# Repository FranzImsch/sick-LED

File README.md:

# Sick LED Driver

## [Schematic](https://franz.science/sick-LED/Schematic.pdf)
## [iBOM](https://franz.science/sick-LED/Hardware/KiCad-Files/bom/index.html)
  
**\*Work in progress\***

Six channel LED driver board that is built around the [LZ7-04-M2PD](https://www.osram.com/ecat/LED%20ENGIN%20LuxiGen%20LZ7-04M2PD/com/en/class_pim_web_catalog_103489/prd_pim_device_13582430/) on MCPCB from LED Engin.

 It's a 60W LED with six colours, which can be used to do some adjustable white experiments due to the relatively full spectrum of the LED (at least compared to a normal RGB-LED): 

The project's objective is not to build an LED that is as bright as possible but to create a dev board that makes it easy to study RGBALC LEDs. Thus, the board is powered via USB-PD and programmed with Arduino.

## Hardware
The PCB is mounted on a heatsink (100x100x40mm black anodised aluminium) using four M3 screws. Two 40mm fans could be attached to the heatsink and powered using the provided 2.54mm headers (the thermal characteristics of the whole design have not been tested yet).  

### Known (Hardware) Bugs
* Each PWM Channel had to be pulled down with a 4.7kΩ resistor.
* FAN1 pin (PB5, TIM3_CH2) cannot be used as PWM output when Hardware-I2C is initialised (Ch. 2.8.7 [ST Errata Sheet](https://www.st.com/resource/en/errata_sheet/es093-stm32f100x4-stm32f100x6-stm32f100x8-and-stm32f100xb-low-and-mediumdensity-value-line-device-limitations-stmicroelectronics.pdf)).

### Fusion360 online viewer
https://a360.co/2VWAmD9

#### LED Driver (BP1808)
\*Docu\*

#### MCU
\*Docu\*

#### USB-C PD Chip
\*Docu\*

#### Buck Converter
\*Docu\*

#### RS-485 Transceiver
\*Docu\*

#### Microphone Amplifier
\*Docu\*

#### Light Sensor
\*Docu\*

## Software
To this point, the software is very basic. It allows the individual channels to be controlled from a computer (Linux or macOS) with [QLC+](https://www.qlcplus.org). It therefore pretends to be a nanoDMX device (No nanoDMX implementation in QLC+ on Windows, apparently).  
The buttons, microphone, light sensor and DMX interface are not yet implemented.  
The software should be rewritten using STM32Cube framework (in progress™).

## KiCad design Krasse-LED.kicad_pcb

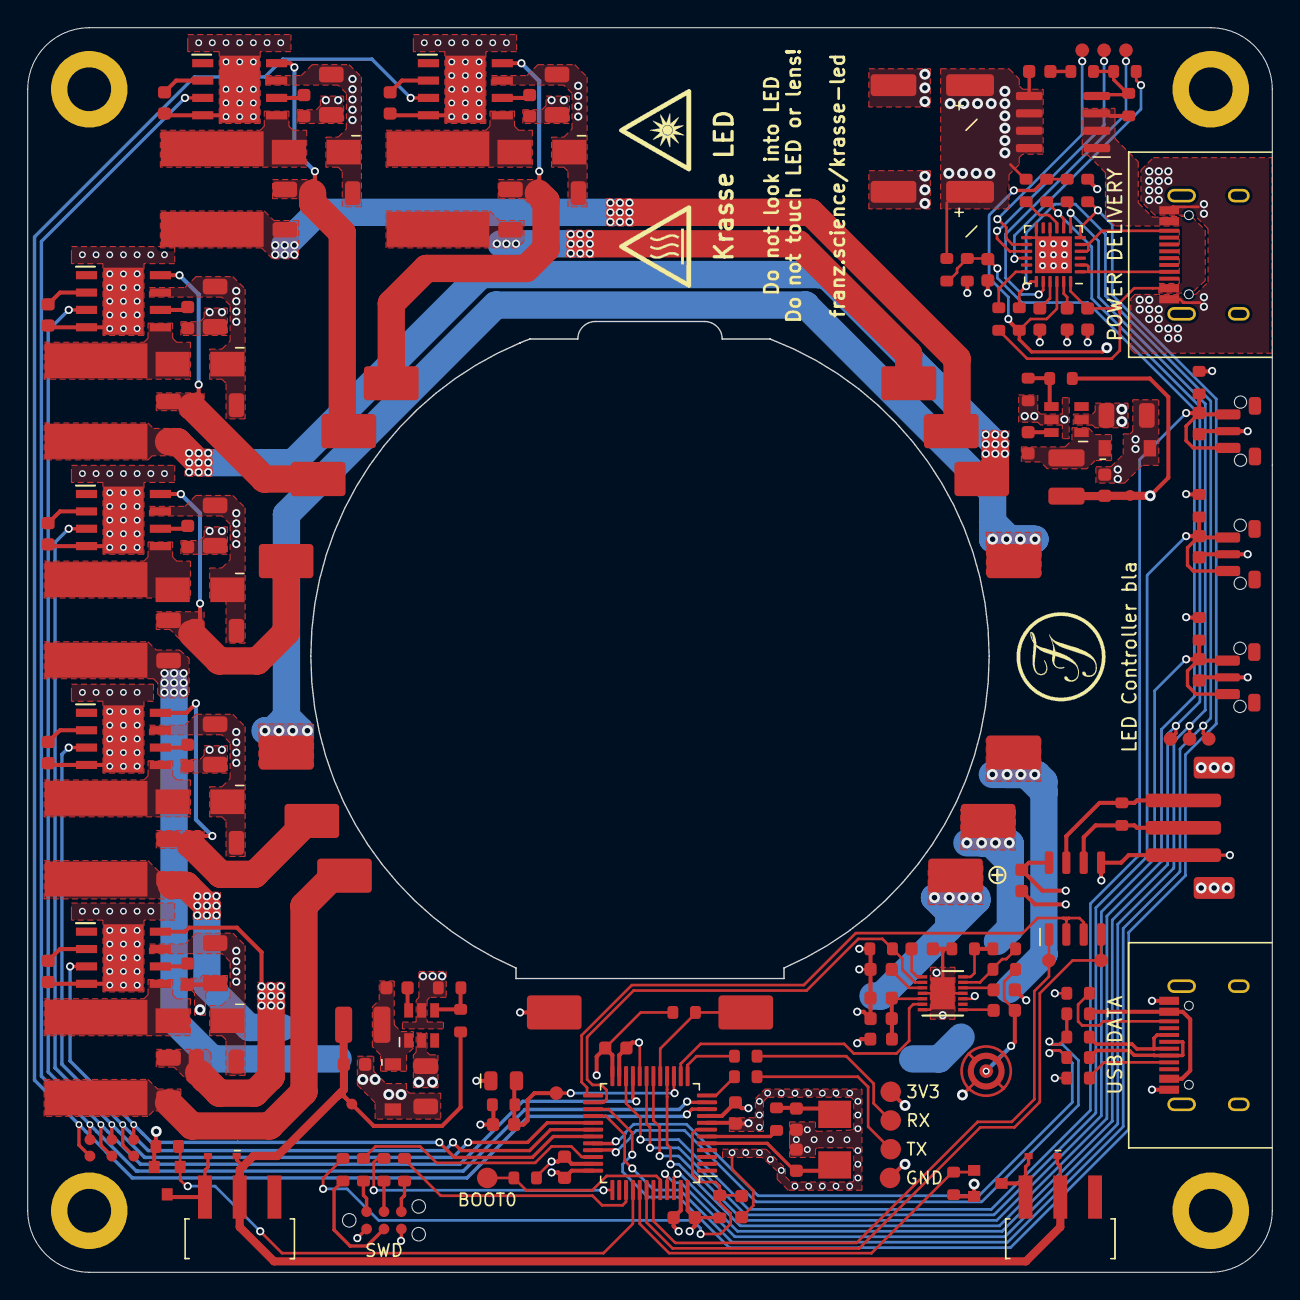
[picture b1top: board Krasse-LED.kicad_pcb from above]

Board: 4 copper layers, 91.0 x 91.0 mm, 175 parts (0 on the bottom side), 112 nets.

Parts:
C1, C2, C46, C54: 22nF; C_0603_1608Metric
C3, C4, C5: 100nF (Y5V); C_0603_1608Metric
C6, C8, C10, C12, C16, C17, C18, C19, C52: 100nF; C_0603_1608Metric
C7: 0.47µF; C_0603_1608Metric
C9: 2.2µF; C_0603_1608Metric
C11, C21, C28, C29, C30, C31, C32, C44, C45: 1µF; C_0603_1608Metric
C13, C38, C39, C40, C41, C42: 2.2µF; C_1206_3216Metric
C14, C15: 30pF; C_0603_1608Metric
C20, C23, C24, C25, C26, C27: 4.7nF; C_0603_1608Metric
C22, C33, C34, C35, C36, C37, C47, C50: 10µF; C_1206_3216Metric
C43: 47nF; C_0603_1608Metric
C48, C53: 15µF; C_Elec_6.3x5.5_WE
C49, C51, C55: 4.7µF; C_0603_1608Metric
D1, D3, D4, D5, D6, D7: SS34; D_SMA
D2: LZ7-04M2PD-PCB
D8, D9: DSS34; D_SOD-123
D11, D12: 1N4148WS; D_SOD-323
FB1: 120Ω; L_0603_1608Metric
H1, H2, H3, H4: M3; MountingHole_3.2mm_M3_DIN965_Pad
J2: TC2030; Tag-Connect_TC2030-IDC-NL_2x03_P1.27mm_Vertical
J3: DMX; JST_PH_B3B-PH-SM4-TB_1x03-1MP_P2.00mm_Vertical
J4, J6: USB_C_Receptacle_USB2.0; USB_C_Receptacle_HRO_TYPE-C-31-M-12
J7: FAN 1; PinHeader_1x03_P2.54mm_Horizontal_SMD_Pin1Left
J8: FAN 2; PinHeader_1x03_P2.54mm_Horizontal_SMD_Pin1Left
L1, L2, L3, L4, L5, L6: 10µH; L_Chilisin_8040
L7, L8: 4.7µH; L_1210_3225Metric
MK1: Microphone_Condenser; B4013AM423-093
Q1: Senba SMD0805-20; LED_0805_2012Metric
Q2: AO4407A; SOIC-8_3.9x4.9mm_P1.27mm
Q3, Q4: AO3400A; SOT-23
R1, R8, R38: 100kΩ; R_0603_1608Metric
R2: 18kΩ; R_0603_1608Metric
R3, R4, R5, R12: 10k; R_0603_1608Metric
R6: ca. 10k; R_0603_1608Metric
R7: 6.2kΩ; R_0603_1608Metric
R9: 150kΩ; R_0603_1608Metric
R10: 2.21kΩ; R_0603_1608Metric
R11: 120Ω; R_0603_1608Metric
R13, R19, R20, R21, R22: 0.2Ω; R_1206_3216Metric
R14, R17: 5.1kΩ; R_0603_1608Metric
R15, R16: 20Ω; R_0603_1608Metric
R18, R31, R32, R45: 4.7kΩ; R_0603_1608Metric
R23: 0.21Ω; R_1206_3216Metric
R24, R25, R26, R27, R33, R34: 22Ω; R_0603_1608Metric
R28, R29, R36, R41, R44: 10kΩ; R_0603_1608Metric
R30: 0Ω; R_0603_1608Metric
R35, R37: 1kΩ; R_0603_1608Metric
R39: 22kΩ; R_0603_1608Metric
R40: 100Ω; R_0603_1608Metric
R42, R46: 50kΩ; R_0603_1608Metric
R43: 16.265kΩ; R_0603_1608Metric
R47: 3.62kΩ; R_0603_1608Metric
SW1, SW2, SW3: SW_Push; SW_Push_1P1T-MP_NO_Horizontal_Alps_SKRTLAE010
TP1: RX1; TestPoint_Pad_D1.0mm
TP2: TX1; TestPoint_Pad_D1.0mm
TP3: SDA; TestPoint_Pad_D1.0mm
TP4: SCL; TestPoint_Pad_D1.0mm
TP6: Light Sensor; TestPoint_Pad_D1.0mm
TP7: BOOT 0; TestPoint_Pad_D1.5mm
TP8: R; TestPoint_Pad_D0.8mm
TP9: B; TestPoint_Pad_D0.8mm
TP10: G; TestPoint_Pad_D0.8mm
TP11: L; TestPoint_Pad_D0.8mm
TP12: A; TestPoint_Pad_D0.8mm
TP13: C; TestPoint_Pad_D0.8mm
TP14: ALERT; TestPoint_Pad_D1.0mm
TP15: PWROK2; TestPoint_Pad_D1.0mm
TP16: PWROK3; TestPoint_Pad_D1.0mm
TP17: GPIO; TestPoint_Pad_D1.0mm
TP18: 3.3V; TestPoint_Pad_D0.8mm
TP19: 12V; TestPoint_Pad_D0.8mm
TP20: 3.3V; TestPoint_Pad_D1.5mm
TP21: TX; TestPoint_Pad_D1.5mm
TP22: RX; TestPoint_Pad_D1.5mm
TP23: GND; TestPoint_Pad_D1.5mm
U1: STM32F103C8Tx; LQFP-48_7x7mm_P0.5mm
U2: MAX9814; DFN-14-1EP_3x3mm_P0.4mm_EP1.78x2.35mm
U3: MAX3485; SOP-8_3.9x4.9mm_P1.27mm
U4, U5, U6, U7, U8, U9: BP1808; Texas_HSOP-8-1EP_3.9x4.9mm_P1.27mm
U10, U12: ACT4088; SOT-23-6
U11: STUSB4500QTR; QFN-24-1EP_4x4mm_P0.5mm_EP2.7x2.7mm
Y1: 8MHz; Crystal_SMD_5032-2Pin_5.0x3.2mm

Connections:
+3V3: C10.1, C16.1, C17.1, C18.1, C19.1, C49.1, FB1.1, J2.1, L7.2, Q1.1, R3.2, R4.2, R5.2, R7.1, R29.2, R31.2, R32.1, R42.1, R45.2, TP18.1, TP20.1, U1.9, U1.24, U1.36, U1.48, U2.10, U3.8, U11.22
+12V: C55.1, D11.1, D12.1, J7.2, J8.2, L8.2, R46.1, TP19.1
/3V3-ANALOG: C11.1, C12.1, FB1.2, U2.5
/AGC-Th: R8.2, R9.1, U2.14
/AmpBias: C7.2, U2.12
/Boostrap-3V3: C46.1, U10.6
/Boostrap-12V: C54.1, U12.6
/CC1-DATA: J4.A5, R17.1
/CC1-PD: J6.A5, U11.1, U11.2
/CC2-DATA: J4.B5, R14.1
/CC2-PD: J6.B5, U11.4, U11.5
/COMP-A: C26.2, U8.2
/COMP-B: C23.2, U5.2
/COMP-C: C27.2, U9.2
/COMP-G: C24.2, U6.2
/COMP-L: C25.2, U7.2
/COMP-R: C20.2, U4.2
/D+: J4.A6, J4.B6, R16.2
/D-: J4.A7, J4.B7, R15.2
/DC-Offs-Adj: C9.1, U2.3
/DISCH: R37.2, U11.9
/DMX_N: J3.2, R11.1, U3.6
/DMX_P: J3.1, R11.2, U3.7
/J-CLK: J2.4, R26.2
/J-DIO: J2.2, R25.2
/J-RESET: J2.3, R24.1
/J-SWO: J2.6, R27.2
/LED-A-A: C41.1, D2.6, R22.1, U8.8
/LED-A-C: C41.2, D2.9, L5.2
/LED-B-A: C38.1, D2.2, R19.1, U5.8
/LED-B-C: C38.2, D2.13, L2.2
/LED-C-A: C42.1, D2.8, R23.1, U9.8
/LED-C-C: C42.2, D2.7, L6.2
/LED-G-A: C39.1, D2.3, R20.1, U6.8
/LED-G-C: C39.2, D2.12, L3.2
/LED-L-A: C40.1, D2.4, R21.1, U7.8
/LED-L-C: C40.2, D2.10, L4.2
/LED-R-A: C13.1, D2.1, R13.1, U4.8
/LED-R-C: C13.2, D2.14, L1.2
/LIME-SERIES: D2.5, D2.11
/MIC+: C6.2, MK1.+, R10.2
/MICBIAS: R9.2, R10.1, U2.13
/MICIN: C6.1, U2.8
/PD-GPIO: TP17.1, U11.15
/PWROK2: TP15.1, U11.20
/PWROK3: TP16.1, U11.14
/RX-IN: R34.2, TP22.1
/SW-3V3: C46.2, D8.1, L7.1, U10.1
/SW-12V: C54.2, D9.1, L8.1, U12.1
/SW-A: D6.2, L5.1, U8.5
/SW-B: D3.2, L2.1, U5.5
/SW-C: D7.2, L6.1, U9.5
/SW-G: D4.2, L3.1, U6.5
/SW-L: D5.2, L4.1, U7.5
/SW-R: D1.2, L1.1, U4.5
/TX-IN: R33.2, TP21.1
/TimingCap: C8.1, U2.1
/VBUS-Disch: R35.1, U11.18
/VBUS-PD: C51.1, J6.A4, J6.A9, J6.B4, J6.B9, Q2.1, Q2.2, Q2.3, R35.2, R38.2, U11.24
/VDD-A: C31.2, U8.6
/VDD-B: C28.2, U5.6
/VDD-C: C32.2, U9.6
/VDD-G: C29.2, U6.6
/VDD-L: C30.2, U7.6
/VDD-R: C21.2, U4.6
BOOT0: R28.1, TP7.1, U1.44
BTN_1: C3.2, R3.1, SW1.1, U1.18
BTN_2: C4.2, R4.1, SW2.1, U1.19
BTN_3: C5.2, R5.1, SW3.1, U1.22
DIM_AMBER: TP12.1, U1.30, U8.3
DIM_BLUE: TP9.1, U1.11, U5.3
DIM_CYAN: TP13.1, U1.31, U9.3
DIM_GREEN: TP10.1, U1.21, U6.3
DIM_LIME: TP11.1, U1.29, U7.3
DIM_RED: TP8.1, U1.10, U4.3
DMX_DE: U1.25, U3.2, U3.3
DMX_IN: TP1.1, U1.43, U3.1
DMX_OUT: TP2.1, U1.42, U3.4
FAN1-PWM: Q4.1, R44.2, U1.40
FAN2-PWM: Q3.1, R41.2, U1.41
GND: C1.1, C2.2, C3.1, C4.1, C5.1, C7.1, C8.2, C9.2, C10.2, C11.2, C12.2, C14.1, C15.2, C16.2, C17.2, C18.2, C19.2, C20.1, C21.1, C22.2, C23.1, C24.1, C25.1, C26.1, C27.1, C28.1, C29.1, C30.1, C31.1, C32.1, C33.2, C34.2, C35.2, C36.2, C37.2, C43.1, C44.1, C45.1, C47.1, C48.-, C49.2, C50.1, C51.2, C53.-, C55.2, D2.1-RT, D8.2, D9.2, J2.5, J3.3, J4.A1, J4.A12, J4.B1, J4.B12, J6.A1, J6.A12, J6.B1, J6.B12, MK1.-, Q3.2, Q4.2, R2.2, R6.2, R8.1, R12.1, R14.2, R17.2, R28.2, R36.2, R41.1, R43.2, R44.1, R47.2, SW1.2, SW2.2, SW3.2, TP23.1, U1.8, U1.20, U1.23, U1.35, U1.47, U2.4, U2.7, U2.11, U2.15, U3.5, U4.4, U4.9, U5.4, U5.9, U6.4, U6.9, U7.4, U7.9, U8.4, U8.9, U9.4, U9.9, U10.5, U11.10, U11.12, U11.13, U11.25, U12.5
I2C1_SCL: R32.2, TP4.1, U1.45, U11.7
I2C1_SDA: R31.1, TP3.1, U1.46, U11.8
LED-Temp: D2.2-RT, R7.2, U1.17
Light: C2.1, Q1.2, R6.1, TP6.1, U1.15
MIC_EN: R12.2, U1.26, U2.2
MIC_OUT: U1.14, U2.6
unnamed: C15.1, R30.2, Y1.2
unnamed: C44.2, U11.21
unnamed: C45.2, U11.23
unnamed: C52.2, R40.1
unnamed: D11.2, J8.1, Q3.3
unnamed: D12.2, J7.1, Q4.3
unnamed: Q2.4, R38.1, R39.1, R40.2
unnamed: R39.2, U11.16
unnamed: R42.2, R43.1, U10.4
unnamed: R46.2, R47.1, U12.4
RESET: C43.2, R24.2, R29.1, U1.7
RX: R34.1, U1.13
SWCLK: R26.1, U1.37
SWDIO: R25.1, U1.34
SWO: R27.1, U1.39
TX: R33.1, U1.12
USB-PD_ALERT: R45.1, TP14.1, U1.28, U11.19
USB-PD_RESET: R36.1, U1.27, U11.6
USB_N: R15.1, U1.32
USB_P: R16.1, R18.2, U1.33
VBUS: J4.A4, J4.A9, J4.B4, J4.B9, R18.1
VCC: C22.1, C33.1, C34.1, C35.1, C36.1, C37.1, C47.2, C48.+, C50.2, C52.1, C53.+, D1.1, D3.1, D4.1, D5.1, D6.1, D7.1, Q2.5, Q2.6, Q2.7, Q2.8, R1.1, R13.2, R19.2, R20.2, R21.2, R22.2, R23.2, R37.1, U4.7, U5.7, U6.7, U7.7, U8.7, U9.7, U10.2, U12.2
VCC-Voltage: C1.2, R1.2, R2.1, U1.16
X1: C14.2, U1.5, Y1.1
X2: R30.1, U1.6

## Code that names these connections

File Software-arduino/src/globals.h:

#pragma once

#include <Arduino.h>

///////////////////
// USER SETTINGS //
///////////////////

#define DEBUG

// LED Settings
#define gamma_correction_factor 2.8
const uint8_t Imax_led[] = {255, 255, 255, 255, 255, 255};

// Safety settings
const byte overtemperature = 70;
const byte fan_on_th = 35;
const byte fan_off_th = 30;

// Fan settings
const byte minPWM_fan = 20; // Intel standard recommendation https://noctua.at/pub/media/wysiwyg/Noctua_PWM_specifications_white_paper.pdf

// USB-PD Settings
// Priority 1
const float USB_Voltage_1 = 20.0;
const float USB_Current_1 = 2.0;

// Priority 2
const float USB_Voltage_2 = 15.0;
const float USB_Current_2 = 2.5;

#ifdef DEBUG
#define DEBUG_PRINT(...) Serial2.print(__VA_ARGS__)
#define DEBUG_PRINTLN(...) Serial2.println(__VA_ARGS__)
#else
#define DEBUG_PRINT(...) NULL
#define DEBUG_PRINTLN(...) NULL
#endif

/////////////////////
// PIN DEFINITIONS //
/////////////////////

/*
 LED pins defined in LED.cpp
*/

#define LED_TEMP PA7

#define FAN1 PB4
#define FAN2 PB5 // conflict with i2c

#define Serial2_TX PA2
#define Serial2_RX PA3

#define DMX_OUT PB6
#define DMX_IN PB7
#define DMX_DE PB12

#define BTN1 PB0
#define BTN2 PB1
#define BTN3 PB11

#define SCL PB8
#define SDA PB9

#define MIC_IN PA4
#define MIC_EN PB13

#define PD_RST PB14
#define PD_ALERT PB15

#define Light_Sensor PA5

#define VCC_Voltage_Pin PA6

///////////////////////
// COLOUR ASSIGNMENT //
///////////////////////

#define red 0
#define green 1
#define blue 2
#define lime 3
#define amber 4
#define cyan 5

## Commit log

2021-08-09 enhanced README
2021-08-11 updated to current project status
2021-08-11 added ibom link
2021-08-16 added spectrum plot and fusion viewer
2021-08-16 added spectrum plot
2021-08-16 fixed a360 link
2021-10-06 added first test software and enhanced documentation
2021-11-26 Readme rendering fixed
2021-11-26 fixing README
